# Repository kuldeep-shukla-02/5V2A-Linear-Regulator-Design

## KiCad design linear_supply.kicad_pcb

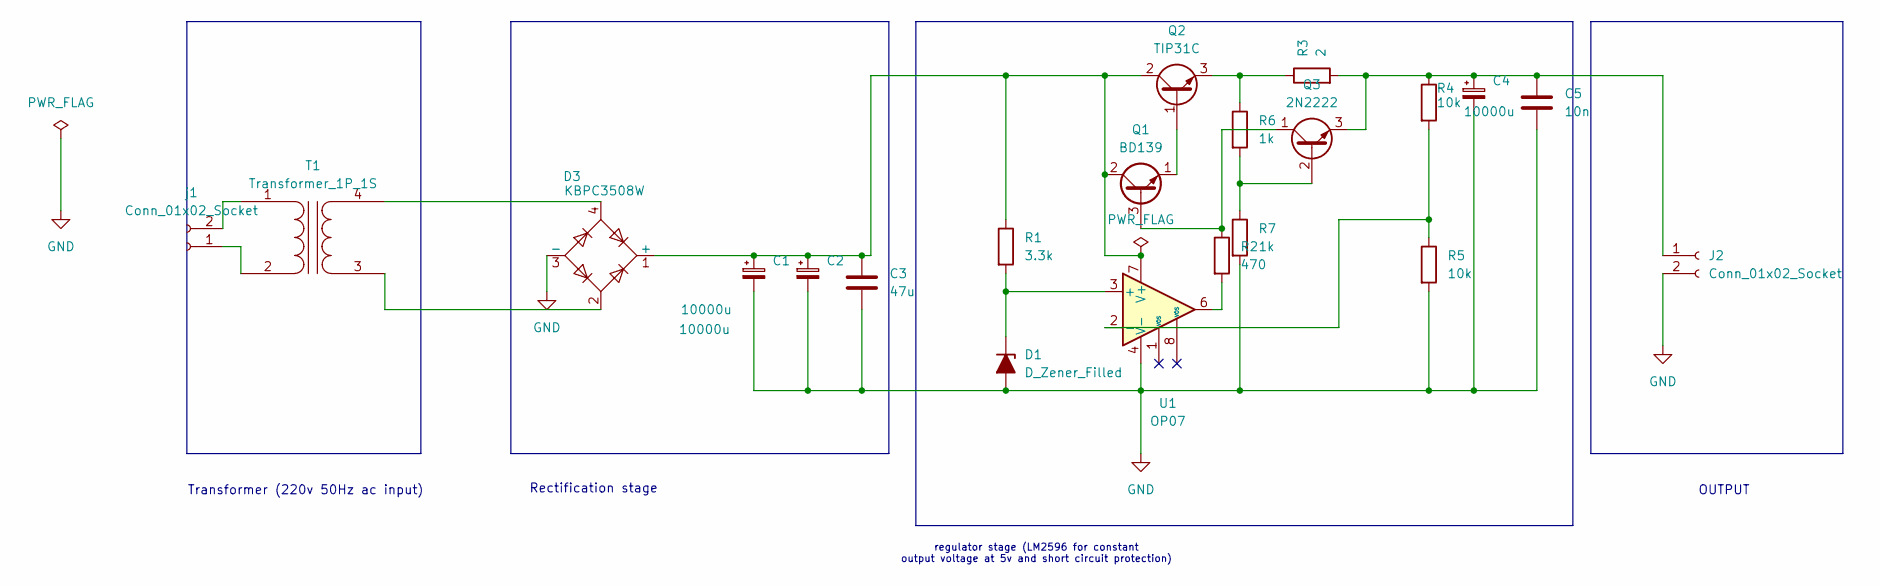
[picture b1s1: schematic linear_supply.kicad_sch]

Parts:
C1, C2, C4: 10000u; CP_Radial_D10.0mm_P2.50mm
C3: 47u; C_Rect_L4.6mm_W4.6mm_P2.50mm_MKS02_FKP02
C5: 10n; C_Rect_L4.6mm_W3.0mm_P2.50mm_MKS02_FKP02
D1: D_Zener_Filled; D_5W_P12.70mm_Horizontal
D3: KBPC3508W; Diode_Bridge_GeneSiC_KBPC_W
J2: Conn_01x02_Socket; JWT_A3963_1x02_P3.96mm_Vertical
Q1: BD139; TO-126-3_Vertical
Q2: TIP31C; TO-220-3_Vertical
Q3: 2N2222; TO-92_Inline
R1: 3.3k; R_Axial_DIN0414_L11.9mm_D4.5mm_P20.32mm_Horizontal
R2: 470; R_Axial_DIN0414_L11.9mm_D4.5mm_P20.32mm_Horizontal
R3: 2; R_Axial_DIN0414_L11.9mm_D4.5mm_P20.32mm_Horizontal
R4, R5: 10k; R_Axial_DIN0414_L11.9mm_D4.5mm_P20.32mm_Horizontal
R6: 1k; R_Axial_DIN0309_L9.0mm_D3.2mm_P15.24mm_Horizontal
R7: 1k; R_Axial_DIN0207_L6.3mm_D2.5mm_P15.24mm_Horizontal
T1: Transformer_1P_1S; Transformer_Zeming_ZMPT101K
U1: OP07; DIP-8_W7.62mm
j1: Conn_01x02_Socket; JWT_A3963_1x02_P3.96mm_Vertical

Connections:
GND: C1.2, C2.2, C3.2, C4.2, C5.2, D1.2 (A), D3.3 (-), J2.2, R5.2, R7.2, U1.4 (V-)
unnamed: D1.1 (K), R1.2, U1.3 (+)
unnamed: C1.1, C2.1, C3.1, D3.1 (+), Q1.2 (C), Q2.2 (C), R1.1, U1.7 (V+)
unnamed: C4.1, C5.1, J2.1, Q3.3 (E), R3.2, R4.1
unnamed: Q1.3 (B), Q3.1 (C), R2.1
unnamed: Q1.1 (E), Q2.1 (B)
unnamed: Q2.3 (E), R3.1, R6.1
unnamed: Q3.2 (B), R6.2, R7.1
unnamed: R2.2, U1.6
unnamed: T1.1 (AA), j1.2
unnamed: T1.2 (AB), j1.1
unnamed: D3.2, T1.3 (SA)
unnamed: D3.4, T1.4 (SB)
unnamed: R4.2, R5.1, U1.2 (-)

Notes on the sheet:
Rectification stage
Transformer (220v 50Hz ac input)
regulator stage (LM2596 for constant output voltage at 5v and short circuit protection)
OUTPUT

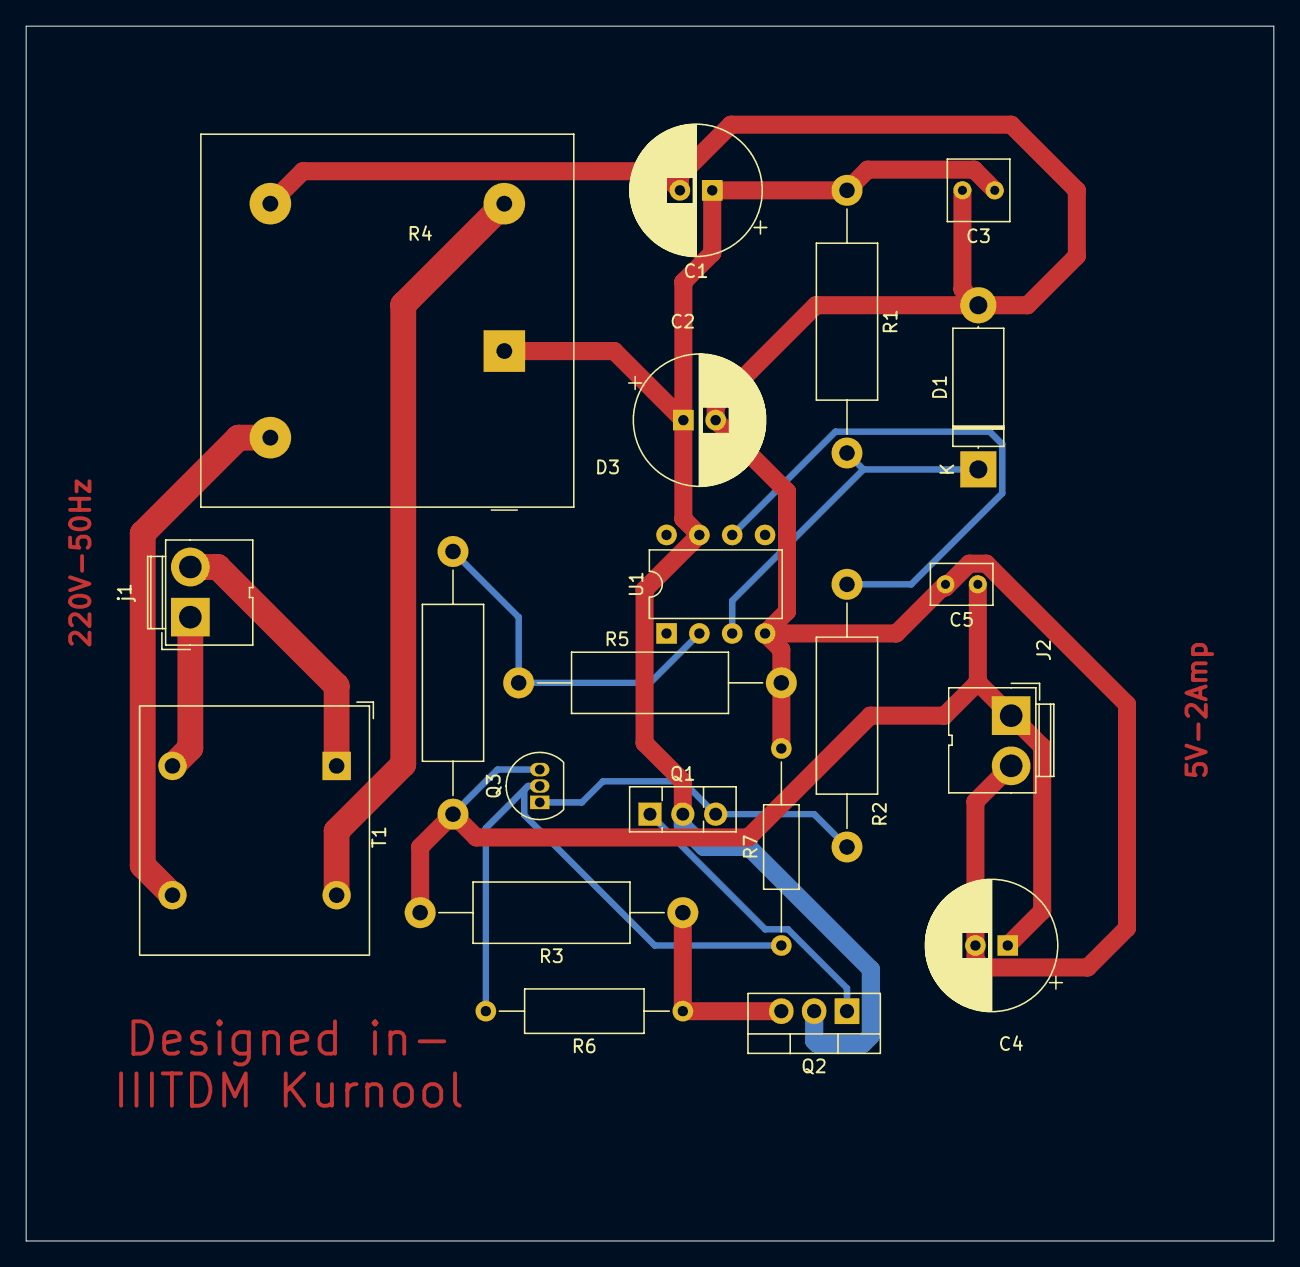
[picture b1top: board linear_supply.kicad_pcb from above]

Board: 2 copper layers, 96.5 x 94.0 mm, 21 parts (0 on the bottom side), 14 nets.

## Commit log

2025-10-08 i uploded this
2025-10-12 i uploded this here
